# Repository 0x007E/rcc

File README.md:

# `RCC` - RGB Color Cube

The `RCC` project is based on a pcb with an [ATtiny402](#additional-information) and two [RGB LEDs](#additional-information) that are controlled via SPI-bus. The cube itself is controlled over a single push-button that enables/disables the cube and can be used to setup the color and intensity of the rgb leds.

| Experience | Level |
|:------------|:-----:|
| Soldering   |  |
| Mechanical  |  |
| Software    |  |

# Manual

| Language | File                                                                        | Description                                        |
|:--------:|:---------------------------------------------------------------------------:|:--------------------------------------------------:|
| English  | [pdf](https://github.com/0x007E/rcc/releases/latest/download/manual.en.pdf) | Assembly of PCB/housing and programming of the RCC |
| German   | [pdf](https://github.com/0x007E/rcc/releases/latest/download/manual.de.pdf) | Assembly of PCB/housing and programming of the RCC |

# Simulator

With the [RCC-Simulator](https://0x007e.github.io/rcc-simulator/) different functions (e.g. power-on/-off, ...) can be simulated within a webpage.

# Downloads

| Type      | File               | Description              |
|:---------:|:------------------:|:-------------------------|
| Schematic | [pdf](https://github.com/0x007E/rcc/releases/latest/download/schematic.pdf) / [cadlab](https://cadlab.io/project/29642/main/files) | Schematic files |
| Board | [pdf](https://github.com/0x007E/rcc/releases/latest/download/pcb.pdf) / [cadlab](https://cadlab.io/project/29642/main/files) | Board file |
| Drill | [pdf](https://github.com/0x007E/rcc/releases/latest/download/drill.pdf) | Drill file |
| PCB | [zip](https://github.com/0x007E/rcc/releases/latest/download/kicad.zip) / [tar](https://github.com/0x007E/rcc/releases/latest/download/kicad.tar.gz) | KiCAD/Gerber/BoM/Drill files |
| Mechanical | [zip](https://github.com/0x007E/rcc/releases/latest/download/freecad.zip) / [tar](https://github.com/0x007E/rcc/releases/latest/download/freecad.tar.gz) | FreeCAD/Housing and PCB (STEP) files     |
| Firmware | [zip](https://github.com/0x007E/rcc/releases/latest/download/firmware.zip) / [tar](https://github.com/0x007E/rcc/releases/latest/download/firmware.tar.gz) | Firmware for ATtiny402 |

# Hardware

There are two parts of the hardware. The pcb and the housing of the `RCC`. The pcb is created with [KiCAD](#additional-information) and the housing with `FreeCAD`. The software is programmed with [Microchip (Atmel) Studio](#additional-information). All files are built with `github actions` so that they are ready for a production environment. The housing is printed with a 3D-printer (`Dremel 3D40`).

## PCB

The circuit board is populated on both sides (Top, Bottom). The best way for soldering the `SMD` components is within a vapor phase soldering system and for the `THT` components with a standard soldering system.

### Top Layer

### Bottom Layer

## Mechanical

The housing has a tolerance of `0.2mm` on each side of the case. So the pcb should fit perfectly in the housing. The tolerance can be modified with `FreeCAD` in the `Parameter` Spreadsheet.

### Assembled

#### Exploded

# Programming/Setup

The `RCC` is powerd with a `3V` battery (`CR2032`). It can be programmed over [UPDI](#additional-information) on `TP1`. The firmware for the cube can be downloaded in the [download section](#downloads).

``` bash
#                                                          +-----------+      +---------------------+
#                                                          |    U  +---+---+  |                     |
#     +---------------------+                              |    S  |  USB  |--+ +-----------------+ |
#     |                     |                              |    B  +---+---+  | | AVR-Dude        | |
#     |    RCC - Color Cube |         +----------+         |    /      |      | | ~~~~~~~~        | |
#     |                  +--+--+   +--+--+  U    |         |    U      |      | | ~~~~~           | |
#     |              VCC | TP3 +---+ VCC |  P  +--+--+  +--+--+ A      |      | | ~~~~~~~~~~~~    | |
#     |              GND | TP2 +---+ GND |  D  | GND +--+ GND | R      |      | |                 | |
#     |                  +--+--+   +--+--+  I  | VCC +--+ VCC | T      |      | +-----------------+ |
#     |                     |         |        +-----+  +-----+ A      |      |                     |
#     |                  +--+--+   +--+--+     | RxD +--+ RxD | +------+      | Computer            |
#     |             UPDI | TP1 +---+ PDI |     | TxD +--+ TxD | |5V/3V3|      |                     |
#     |                  +--+--+   +--+--+     +--+--+  +--+--+ +------+      +---------------------+
#     +---------------------+         | ADAPTER   |        +----+------+
#                                     +-----------+
```

## FUSES

| Register  | Value  |
|:---------:|:------:|
| `WDTCFG`  | `0x00` |
| `BODCFG`  | `0x00` |
| `OSCCFG`  | `0x03` |
| `TCD0CFG` | `0x00` |
| `SYSCFG0` | `0xF5` |
| `SYSCFG1` | `0x00` |
| `APPEND`  | `0x00` |
| `BOOTEND` | `0x00` |

# Software

The leds are controlled by `SPI`. The interface is displayed in the [dataflow](#dataflow-diagram) diagram. There is a pre-configured firmware to use the cube or a library to implement own solutions.

> A documentation of the code can be found here [https://0x007e.github.io/rcc](https://0x007e.github.io/rcc).

## Dataflow diagram

## Library (`led.h`)

With the attached `led` library it is quiet easy to use the cube for own implementations. To setup the led library for the cube implement the header file.

``` c
#define F_CPU 20000000UL

#include <avr/io.h>
#include <util/delay.h>

#include "./hal/avr0/system/system.h"
#include "./led/led.h"

LED_Data led1  = {
	0x01,
	0x0F,
	0x00,
	0x0A
};

LED_Data led2  = {
	0x01,
	0x00,
	0x0F,
	0x0A
};

int main(void)
{
    system_init();
    led_init();
    // ...

    while(1)
    {
        led_blink(LED_Position_Left | LED_Position_Right_Alternating, led_status_color(LED_Status_Ready, LED_MIN_INTENSITY), LED_Delay_MS_200, 2);

        LED_SOF();
        led_data(led1);
        led_data(led2);
        LED_EOF();

        _delay_ms(2000);
    }
}
```

# Additional Information

| Type       | Link               | Description              |
|:----------:|:------------------:|:-------------------------|
| ATtiny402  | [pdf](https://ww1.microchip.com/downloads/en/DeviceDoc/ATtiny202-402-AVR-MCU-with-Core-Independent-Peripherals_and-picoPower-40001969A.pdf) | ATtiny microcontroller |
| T3A33BRG   | [pdf](https://mm.digikey.com/Volume0/opasdata/d220001/medias/docus/6794/3147_T3A33BRG-H9C0002X1U1930.pdf) | RGB Color LED |
| Atmel ICE  | [pdf](https://ww1.microchip.com/downloads/en/DeviceDoc/Atmel-ICE_UserGuide.pdf) | Atmel ICE datasheet |
| UPDI       | [web](https://github.com/0x007e/updi) | UPDI-Adapter with AVR-Dude |
| Microchip Studio | [web](https://www.microchip.com/en-us/tools-resources/develop/microchip-studio) | Download page for Microchip Studio |
| KiCAD | [web](https://www.kicad.org/) | KiCAD project page |
| FreeCAD | [web](https://www.freecad.org/) | FreeCAD project page |

---

R. GAECHTER

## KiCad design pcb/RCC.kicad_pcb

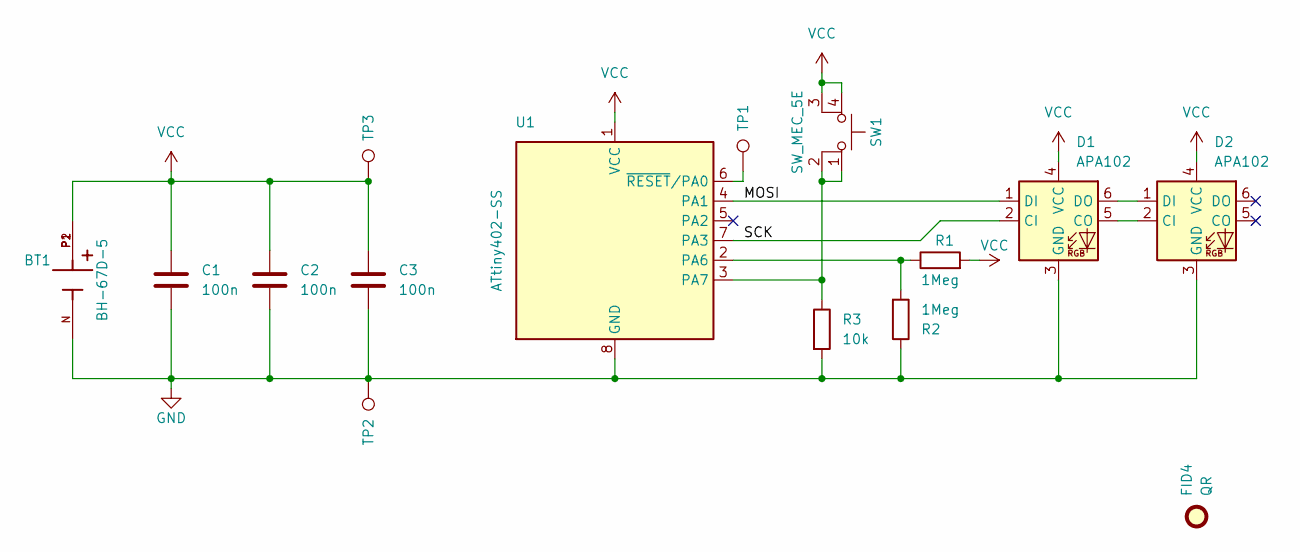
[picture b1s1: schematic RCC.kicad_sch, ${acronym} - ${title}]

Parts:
BT1: BH-67D-5; BAT_BH-67D-5
C1, C2, C3: 100n; C_1206_3216Metric
D1, D2: APA102; LED_RGB_5050-6
FID4: QR; QR_0x007e_small
R1, R2: 1Meg; R_1206_3216Metric
R3: 10k; R_1206_3216Metric
SW1: SW_MEC_5E; SW_PTS530_GK055_SMTR_LFS
TP1, TP2, TP3: TestPoint; TestPoint_Pad_D1.5mm
U1: ATtiny402-SS; SOIC-8_3.9x4.9mm_P1.27mm

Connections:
/MOSI: D1.1 (DI), U1.4 (PA1)
/SCK: D1.2 (CI), U1.7 (PA3)
GND: BT1.N, C1.2, C2.2, C3.2, D1.3 (GND), D2.3 (GND), R2.1, R3.2, TP2.1, U1.8 (GND)
unnamed: D1.5 (CO), D2.2 (CI)
unnamed: D1.6 (DO), D2.1 (DI)
unnamed: R1.1, R2.2, U1.2 (PA6)
unnamed: R3.1, SW1.1, SW1.2, U1.3 (PA7)
unnamed: TP1.1, U1.6 (~RESET/PA0)
VCC: BT1.P1, BT1.P2, C1.1, C2.1, C3.1, D1.4 (VCC), D2.4 (VCC), R1.2, SW1.3 (K), SW1.4 (A), TP3.1, U1.1 (VCC)

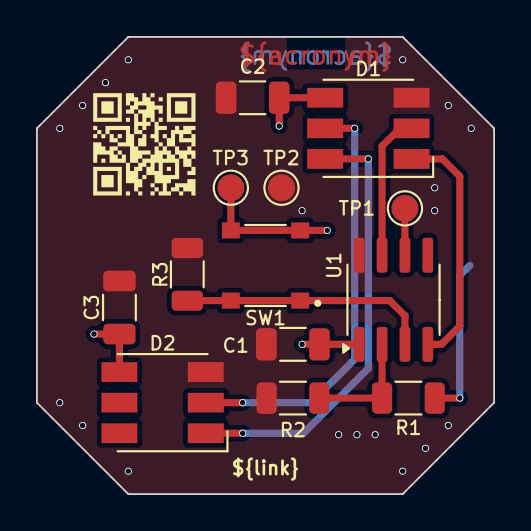
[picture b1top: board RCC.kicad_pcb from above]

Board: 2 copper layers, 25.4 x 25.4 mm, 15 parts (1 on the bottom side), 9 nets.

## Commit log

2025-09-28 Add .vscode folder exclusion
2025-09-29 Fix missing settings
2025-09-29 Change value of R3
2025-10-01 Disable floating pins during sleep
2025-10-03 Exclude images
2025-10-03 Change intensity setup delay time
2025-10-03 Add assembly explosion
2025-10-03 Add README.md
2025-10-03 Change PCB
2025-10-04 Fix ERC error
2025-10-04 Change status text
2025-10-04 Add build pipeline
2025-10-04 Fix LICENSE path
2025-10-04 Fix problems if lib and project are in same path
2025-10-04 Move deletion of same path to function
2025-10-04 Change path of main
2025-10-04 Add release pipeline
2025-10-04 Change kibot config file path
2025-10-04 Center the PCB in the middle of the drawing sheet
2025-10-04 Upscale the pcb for better readability
2025-10-04 Optimize fabrication text position
2025-10-04 Add text variables to pcb
2025-10-07 Change partlist vendors
2025-10-11 Add social image
2025-10-12 Add auto build of code documentation
2025-10-12 Outsourcing defines and includes to main.h
2025-10-12 Add a doxygen description to main header/source
2025-10-12 Add a link to doxygen
2025-10-12 Add dimensioning to test points
2025-10-24 Change firmware pipeline
2025-10-27 Adapt .gitignore
2025-10-27 Add value to BOM
2025-10-29 Add DeepWiki badge
2025-10-29 Extend PTS530 fabrication layer
2025-10-30 Add documentation
2025-10-30 Add LaTeX to build pipeline
2025-10-30 Change table spacing
2025-10-30 Change documentation filename
2025-10-30 Adapt changed documentation filename
2025-10-30 Add LaTeX to release pipeline
2025-10-30 Add manual section
2025-11-10 Add washers
2025-11-11 Change rgb led color
2025-11-11 Ignore single button press
2025-11-12 Add link to simulator
2025-11-12 Text revision
2025-11-13 Change battery empty value
2025-11-14 Extend scale of generated pdfs
2025-11-14 Add pdf overlay to build pipeline
2025-11-14 Add pdf overlay to release pipeline

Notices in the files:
README.md:
License CC By-NC-SA
License GPLv3
parts and their libraries:
license: CC BY-NC-SA 4.0
